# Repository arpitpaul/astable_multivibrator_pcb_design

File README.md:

# astable_multivibrator_pcb_design

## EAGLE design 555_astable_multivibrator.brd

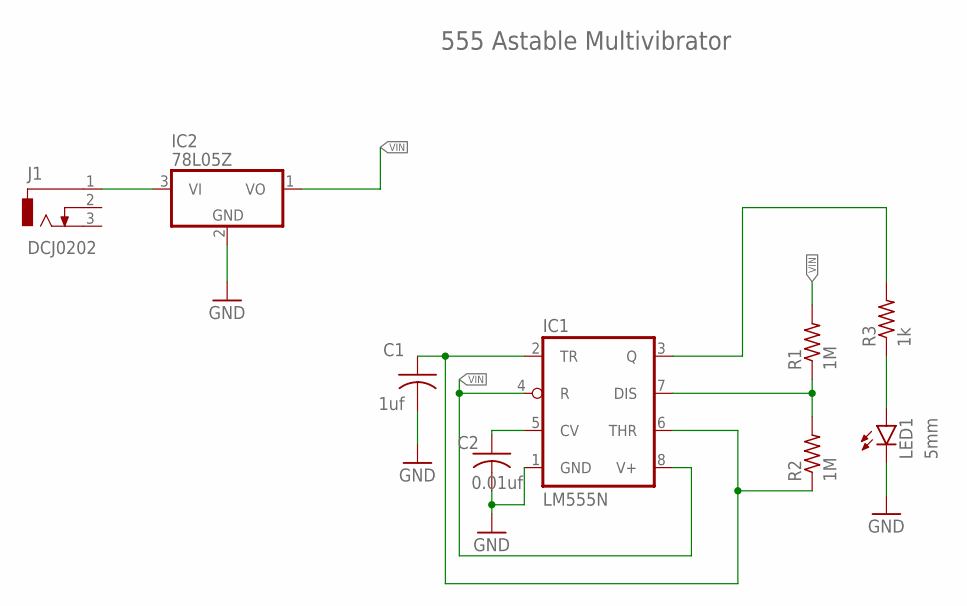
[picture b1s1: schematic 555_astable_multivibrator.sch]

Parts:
C1: 1uf; C050-024X044
C2: 0.01uf; C050-024X044
IC1: LM555N; DIL08
IC2: 78L05Z; TO92
J1: DCJ0202
LED1: 5mm; LED5MM
R1, R2: 1M; 0207/2V
R3: 1k; 0207/2V

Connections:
5V: C1.1, IC1.2 (TR), IC1.6 (THR), R2.1
GND: C1.2, C2.2, IC1.1 (GND), IC2.2 (GND), LED1.K (C)
unnamed: IC1.7 (DIS), R1.1, R2.2
unnamed: IC2.3 (VI), J1.1
unnamed: C2.1, IC1.5 (CV)
unnamed: IC1.3 (Q), R3.2
unnamed: LED1.A, R3.1
VIN: IC1.4 (R), IC1.8 (V+), IC2.1 (VO), R1.2

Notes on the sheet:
555 Astable Multivibrator

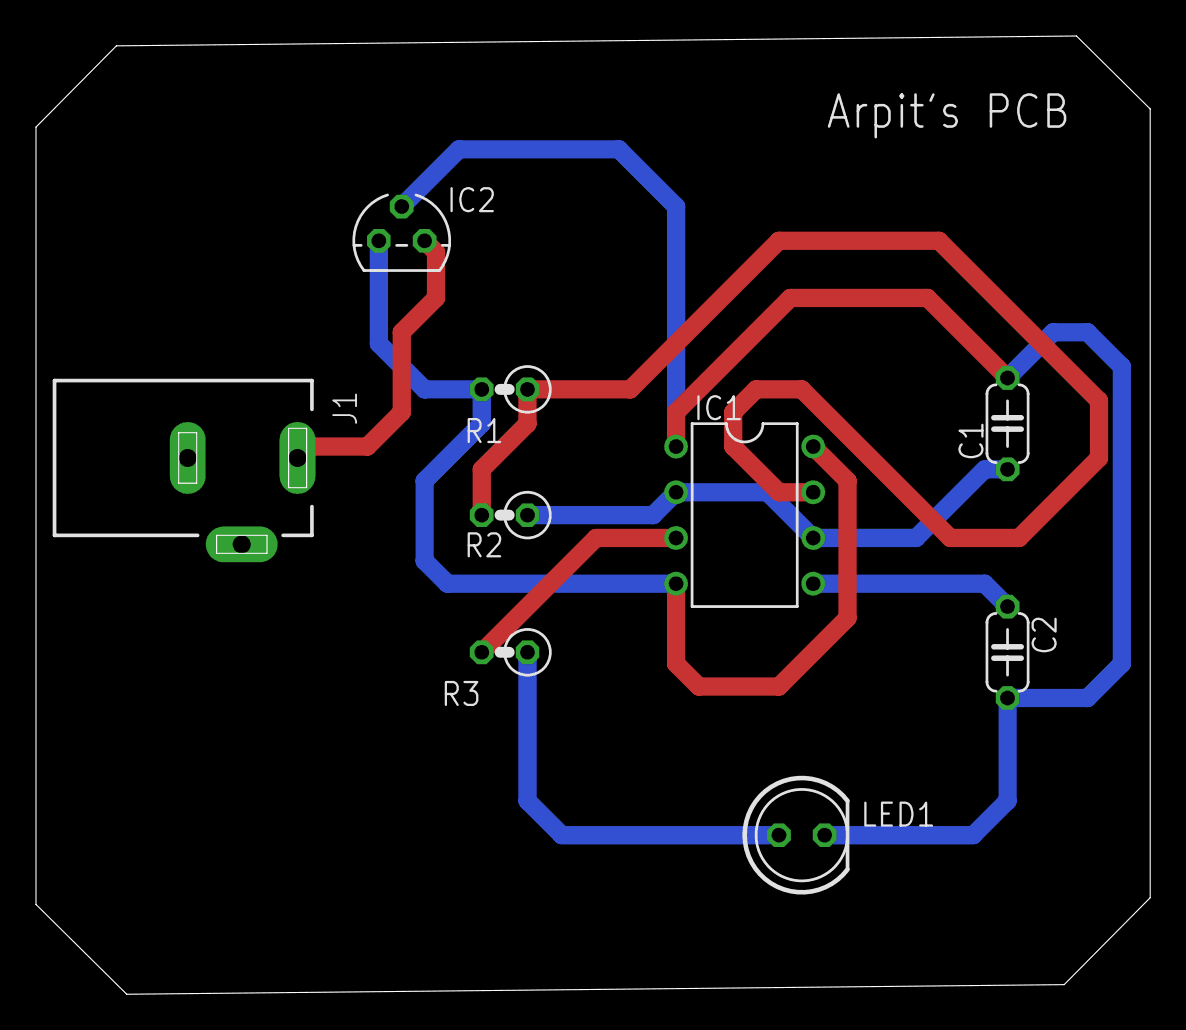
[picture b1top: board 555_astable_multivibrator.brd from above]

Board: 2 copper layers, 61.9 x 53.2 mm, 9 parts (0 on the bottom side), 8 nets.
